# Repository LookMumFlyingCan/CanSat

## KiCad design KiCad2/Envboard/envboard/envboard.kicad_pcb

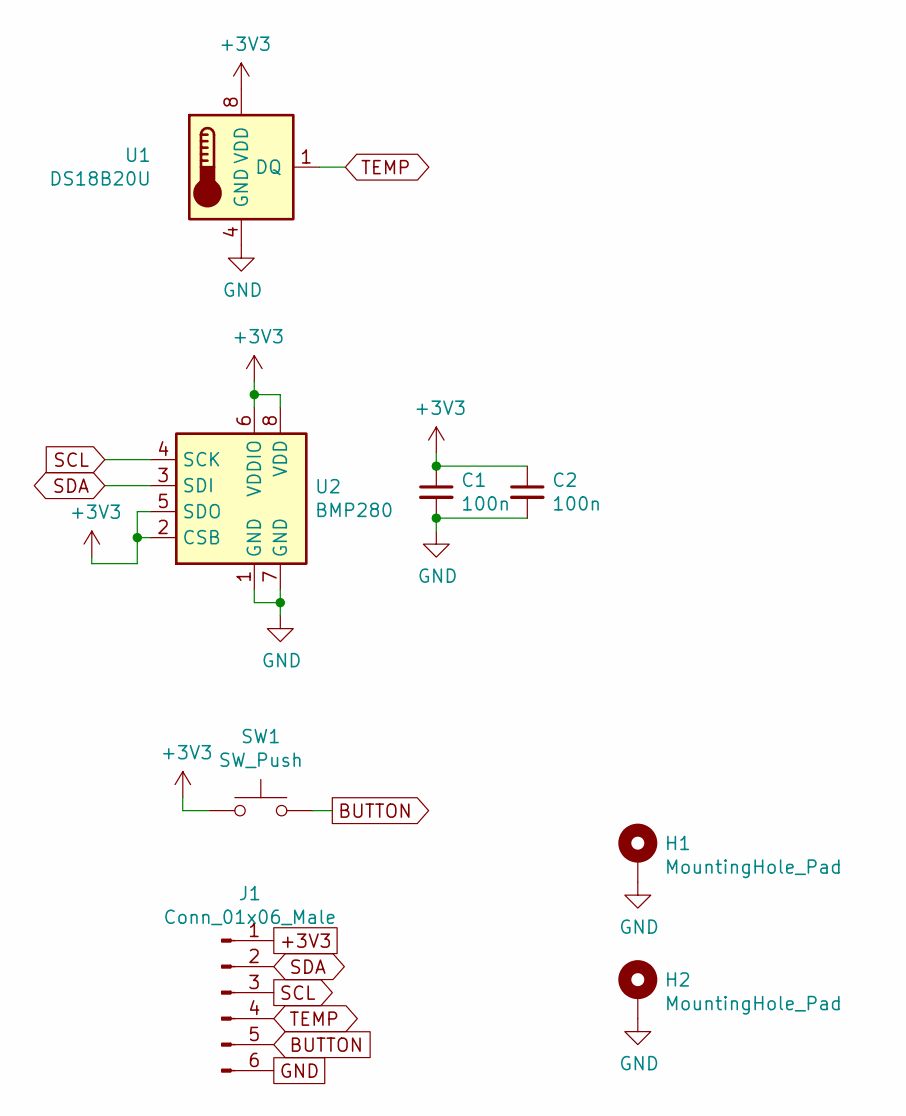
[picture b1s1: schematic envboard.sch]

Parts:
C1, C2: 100n; C_0603_1608Metric
H1, H2: MountingHole_Pad; MountingHole_2.2mm_M2_Pad_Via
J1: Conn_01x06_Male; JST_SH_BM06B-SRSS-TB_1x06-1MP_P1.00mm_Vertical
SW1: SW_Push; SW_SPST_TAEF-25R-V-T
U1: DS18B20U; MSOP-8_3x3mm_P0.65mm
U2: BMP280; Bosch_LGA-8_2x2.5mm_P0.65mm_ClockwisePinNumbering

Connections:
+3V3: C1.1, C2.1, J1.1, SW1.1, U1.8 (VDD), U2.2 (CSB), U2.5 (SDO), U2.6 (VDDIO), U2.8 (VDD)
BUTTON: J1.5, SW1.2
GND: C1.2, C2.2, H1.1, H2.1, J1.6, U1.4 (GND), U2.1 (GND), U2.7 (GND)
SCL: J1.3, U2.4 (SCK)
SDA: J1.2, U2.3 (SDI)
TEMP: J1.4, U1.1 (DQ)

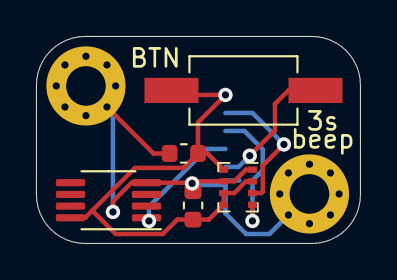
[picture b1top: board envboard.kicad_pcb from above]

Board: 2 copper layers, 18.0 x 11.5 mm, 8 parts (1 on the bottom side), 6 nets.

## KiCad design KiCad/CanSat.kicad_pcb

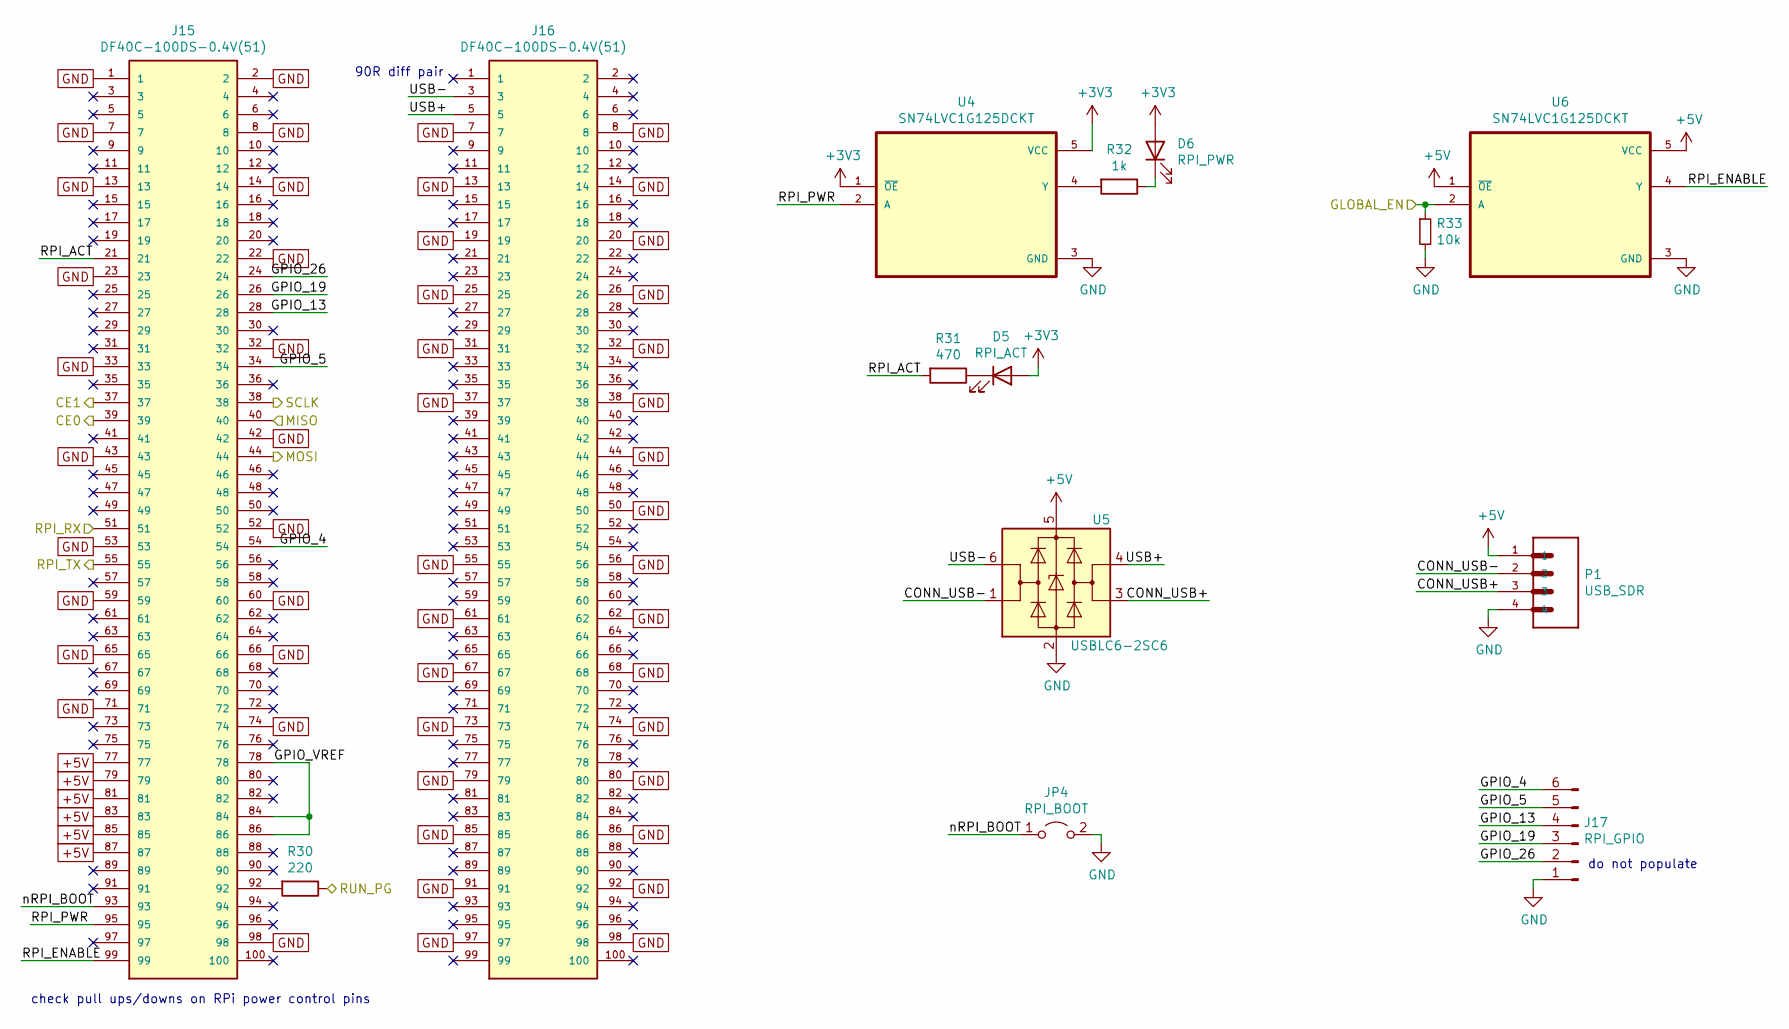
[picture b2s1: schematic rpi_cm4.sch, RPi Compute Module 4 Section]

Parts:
D5: RPI_ACT; LED_0603_1608Metric_Pad1.05x0.95mm_HandSolder
D6: RPI_PWR; LED_0603_1608Metric_Pad1.05x0.95mm_HandSolder
J15, J16: DF40C-100DS-0.4V(51); HRS_DF40C-100DS-0.4V(51)
J17: RPI_GPIO; PinHeader_1x06_P1.00mm_Vertical
JP4: RPI_BOOT; TestPoint_2Pads_Pitch2.54mm_Drill0.8mm
P1: USB_SDR; TE_1734366-1
R30: 220; R_0603_1608Metric_Pad1.05x0.95mm_HandSolder
R31: 470; R_0603_1608Metric_Pad1.05x0.95mm_HandSolder
R32: 1k; R_0603_1608Metric_Pad1.05x0.95mm_HandSolder
R33: 10k; R_0603_1608Metric_Pad1.05x0.95mm_HandSolder
U4, U6: SN74LVC1G125DCKT; SOT65P210X110-5N
U5: USBLC6-2SC6; SOT-23-6

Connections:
+5V: J15.77, J15.79, J15.81, J15.83, J15.85, J15.87, P1.1, U5.5 (VBUS), U6.1 (~OE), U6.5 (VCC); also elsewhere on the board
/Peripherals and Connectors/CLK: J15.38; also elsewhere on the board
/Peripherals and Connectors/MISO: J15.40; also elsewhere on the board
/Peripherals and Connectors/MOSI: J15.44; also elsewhere on the board
/RPi CM4/CE0: J15.39; also elsewhere on the board
/RPi CM4/CE1: J15.37; also elsewhere on the board
/RPi CM4/CONN_USB+: P1.3, U5.3 (I/O2)
/RPi CM4/CONN_USB-: P1.2, U5.1 (I/O1)
/RPi CM4/GLOBAL_EN: R33.1, U6.2 (A); also elsewhere on the board
/RPi CM4/GPIO_4: J15.54, J17.6
/RPi CM4/GPIO_5: J15.34, J17.5
/RPi CM4/GPIO_13: J15.28, J17.4
/RPi CM4/GPIO_19: J15.26, J17.3
/RPi CM4/GPIO_26: J15.24, J17.2
/RPi CM4/GPIO_VREF: J15.78, J15.84, J15.86
/RPi CM4/RPI_ACT: J15.21, R31.2
/RPi CM4/RPI_ENABLE: J15.99, U6.4 (Y)
/RPi CM4/RPI_PWR: J15.95, U4.2 (A)
/RPi CM4/RPI_RX: J15.51; also elsewhere on the board
/RPi CM4/RPI_TX: J15.55; also elsewhere on the board
/RPi CM4/RUN_PG: R30.1; also elsewhere on the board
/RPi CM4/USB+: J16.5, U5.4 (I/O2)
/RPi CM4/USB-: J16.3, U5.6 (I/O1)
/RPi CM4/nRPI_BOOT: J15.93, JP4.1 (A)
unnamed: D5.1 (K), R31.1
unnamed: D6.1 (K), R32.1
unnamed: J15.92, R30.2
unnamed: R32.2, U4.4 (Y)

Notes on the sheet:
90R diff pair
check pull ups/downs on RPi power control pins
do not populate

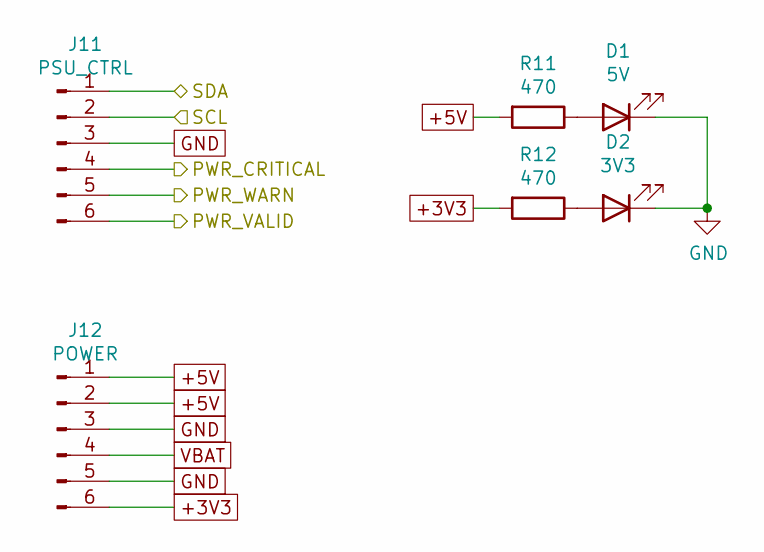
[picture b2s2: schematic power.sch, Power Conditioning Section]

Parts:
D1: 5V; LED_0603_1608Metric_Pad1.05x0.95mm_HandSolder
D2: 3V3; LED_0603_1608Metric_Pad1.05x0.95mm_HandSolder
J11: PSU_CTRL; JST_SH_BM06B-SRSS-TB_1x06-1MP_P1.00mm_Vertical
J12: POWER; JST_PH_S6B-PH-K_1x06_P2.00mm_Horizontal
R11, R12: 470; R_0603_1608Metric_Pad1.05x0.95mm_HandSolder

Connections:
+5V: J12.1, J12.2, R11.2; also elsewhere on the board
/Peripherals and Connectors/SCL: J11.5; also elsewhere on the board
/Peripherals and Connectors/SDA: J11.6; also elsewhere on the board
/Power/PWR_VALID: J11.1; also elsewhere on the board
/Power/PWR_WARN: J11.2; also elsewhere on the board
unnamed: D1.2 (A), R11.1
unnamed: D2.2 (A), R12.1
VBAT: J12.4; also elsewhere on the board

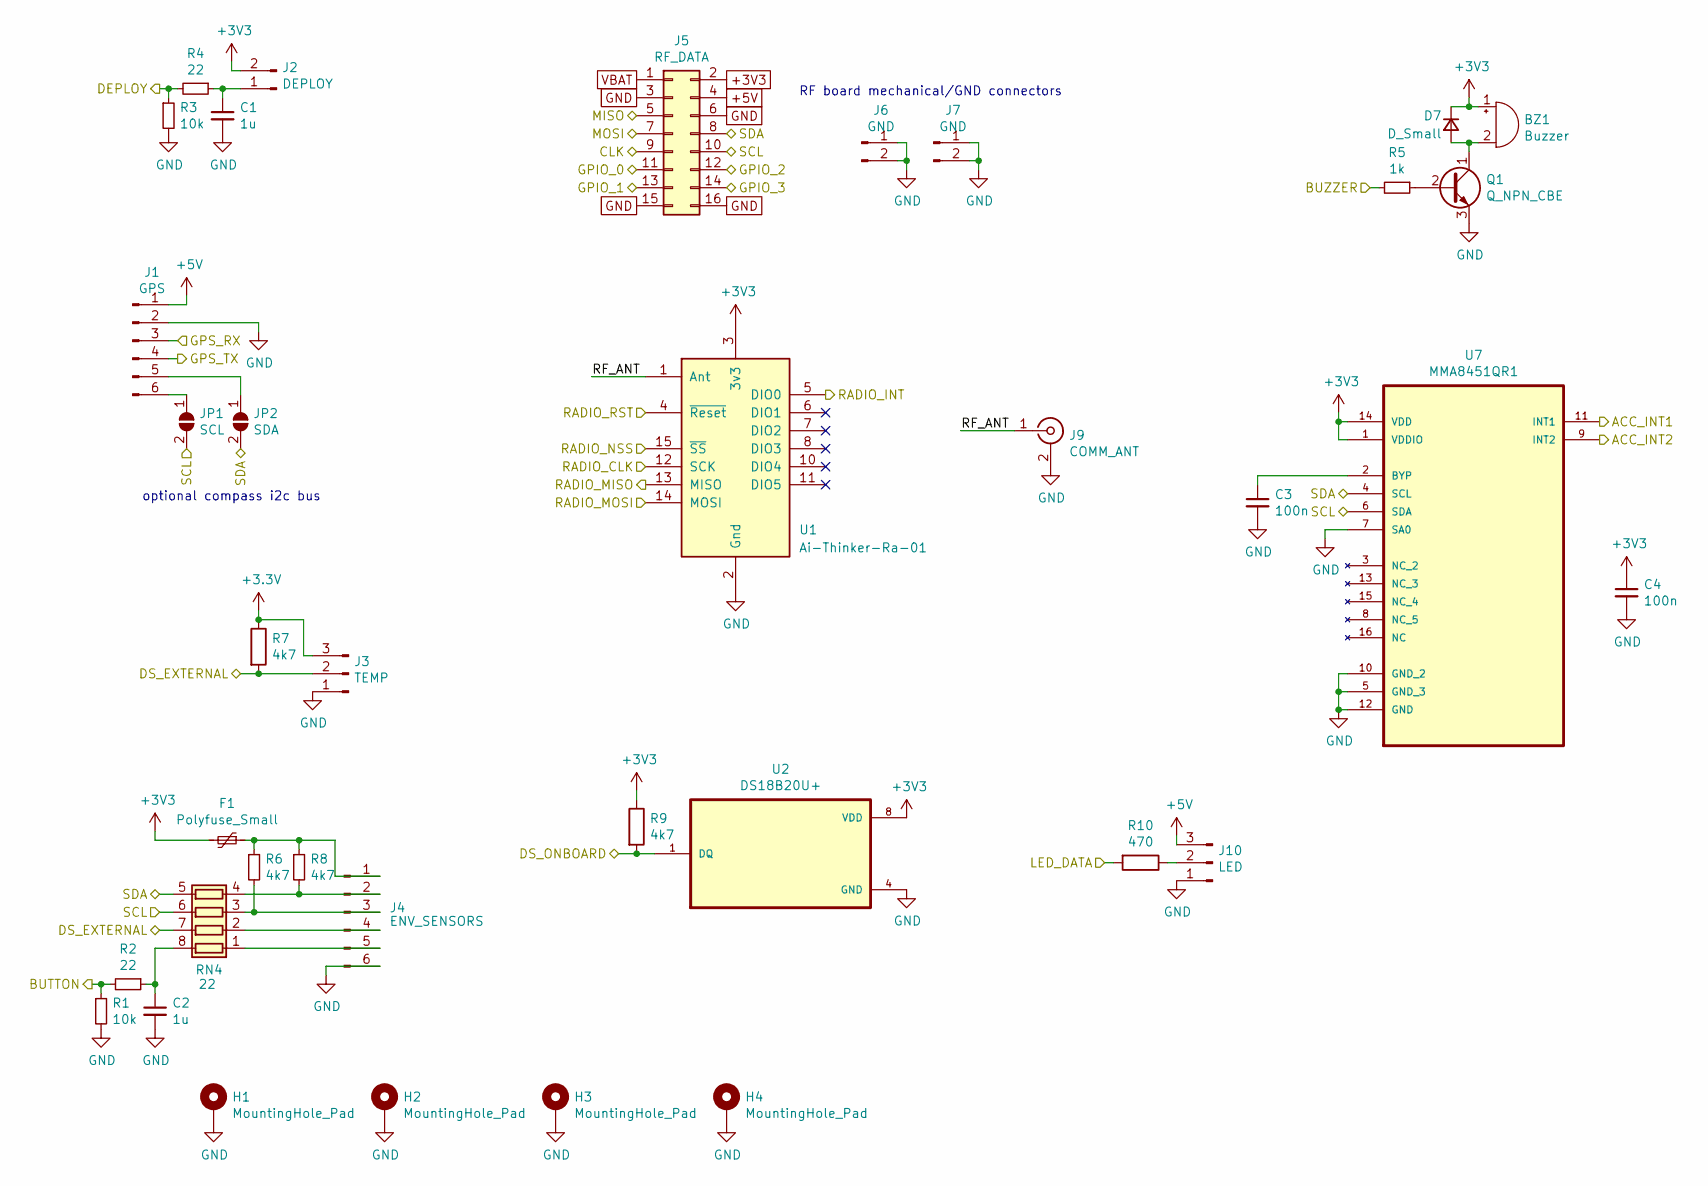
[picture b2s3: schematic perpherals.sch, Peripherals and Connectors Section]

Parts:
BZ1: Buzzer; MagneticBuzzer_INGHAi_GSC4417YA-16R4000
C1, C2: 1u; C_0603_1608Metric_Pad1.05x0.95mm_HandSolder
C3, C4: 100n; C_0603_1608Metric_Pad1.05x0.95mm_HandSolder
D7: D_Small; D_0603_1608Metric_Pad1.05x0.95mm_HandSolder
F1: Polyfuse_Small; Fuse_0603_1608Metric_Pad1.05x0.95mm_HandSolder
H1, H2, H3, H4: MountingHole_Pad; MountingHole_2.7mm_M2.5_Pad_Via
J1: GPS; JST_SH_SM06B-SRSS-TB_1x06-1MP_P1.00mm_Horizontal
J2: DEPLOY; JST_SH_SM02B-SRSS-TB_1x02-1MP_P1.00mm_Horizontal
J3: TEMP; JST_SH_SM03B-SRSS-TB_1x03-1MP_P1.00mm_Horizontal
J4: ENV_SENSORS; JST_SH_SM06B-SRSS-TB_1x06-1MP_P1.00mm_Horizontal
J5: RF_DATA; PinHeader_2x08_P1.27mm_Vertical_SMD
J6, J7: GND; PinHeader_1x02_P2.54mm_Vertical
J9: COMM_ANT; U.FL_Molex_MCRF_73412-0110_Vertical
J10: LED; PinHeader_1x03_P2.54mm_Horizontal
JP1: SCL; SolderJumper-2_P1.3mm_Open_TrianglePad1.0x1.5mm
JP2: SDA; SolderJumper-2_P1.3mm_Open_TrianglePad1.0x1.5mm
Q1: Q_NPN_CBE; SOT-23
R1, R3: 10k; R_0603_1608Metric_Pad1.05x0.95mm_HandSolder
R2, R4: 22; R_0603_1608Metric_Pad1.05x0.95mm_HandSolder
R5: 1k; R_0603_1608Metric_Pad1.05x0.95mm_HandSolder
R6, R7, R8, R9: 4k7; R_0603_1608Metric_Pad1.05x0.95mm_HandSolder
R10: 470; R_0603_1608Metric_Pad1.05x0.95mm_HandSolder
RN4: 22; R_Array_Concave_4x0603
U1: Ai-Thinker-Ra-01; Ai-Thinker-Ra-01-LoRa
U2: DS18B20U+; SOP65P490X110-8N
U7: MMA8451QR1; QFN50P300X300X100-16N; MPN MMA8451QR1

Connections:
+5V: J1.1, J5.4, J10.3; also elsewhere on the board
/Peripherals and Connectors/ACC_INT1: U7.11 (INT1); also elsewhere on the board
/Peripherals and Connectors/ACC_INT2: U7.9 (INT2); also elsewhere on the board
/Peripherals and Connectors/BUTTON: R1.1, R2.2; also elsewhere on the board
/Peripherals and Connectors/BUZZER: R5.2; also elsewhere on the board
/Peripherals and Connectors/CLK: J5.9; also elsewhere on the board
/Peripherals and Connectors/DEPLOY: R3.1, R4.2; also elsewhere on the board
/Peripherals and Connectors/DS_EXTERNAL: J3.2, R7.2, R9.2, RN4.7 (R2.2), U2.1 (DQ); also elsewhere on the board
/Peripherals and Connectors/GPIO_2: J5.12; also elsewhere on the board
/Peripherals and Connectors/GPIO_3: J5.14; also elsewhere on the board
/Peripherals and Connectors/GPS_RX: J1.3; also elsewhere on the board
/Peripherals and Connectors/GPS_TX: J1.4; also elsewhere on the board
/Peripherals and Connectors/LED_DATA: R10.2; also elsewhere on the board
/Peripherals and Connectors/MISO: J5.5; also elsewhere on the board
/Peripherals and Connectors/MOSI: J5.7; also elsewhere on the board
/Peripherals and Connectors/RADIO_CLK: U1.12 (SCK); also elsewhere on the board
/Peripherals and Connectors/RADIO_INT: U1.5 (DIO0); also elsewhere on the board
/Peripherals and Connectors/RADIO_MISO: U1.13 (MISO); also elsewhere on the board
/Peripherals and Connectors/RADIO_MOSI: U1.14 (MOSI); also elsewhere on the board
/Peripherals and Connectors/RADIO_NSS: U1.15 (~SS); also elsewhere on the board
/Peripherals and Connectors/RADIO_RST: U1.4 (~Reset); also elsewhere on the board
/Peripherals and Connectors/RF_ANT: J9.1 (In), U1.1 (Ant)
/Peripherals and Connectors/SCL: J5.10, JP1.2 (B), RN4.6 (R3.2), U7.6 (SDA); also elsewhere on the board
/Peripherals and Connectors/SDA: J5.8, JP2.2 (B), RN4.5 (R4.2), U7.4 (SCL); also elsewhere on the board
/RPi CM4/CE0: J5.11; also elsewhere on the board
/RPi CM4/CE1: J5.13; also elsewhere on the board
unnamed: BZ1.2 (+), D7.2 (A), Q1.1 (C)
unnamed: C1.1, J2.1, R4.1
unnamed: C2.1, R2.1, RN4.8 (R1.2)
unnamed: C3.1, U7.2 (BYP)
unnamed: F1.1, J4.1, R6.1, R8.1
unnamed: J1.5, JP2.1 (A)
unnamed: J1.6, JP1.1 (A)
unnamed: J4.2, R8.2, RN4.4 (R4.1)
unnamed: J4.3, R6.2, RN4.3 (R3.1)
unnamed: J4.4, RN4.2 (R2.1)
unnamed: J4.5, RN4.1 (R1.1)
unnamed: J10.2, R10.1
unnamed: Q1.2 (B), R5.1
VBAT: J5.1; also elsewhere on the board

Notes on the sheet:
optional compass i2c bus
RF board mechanical/GND connectors

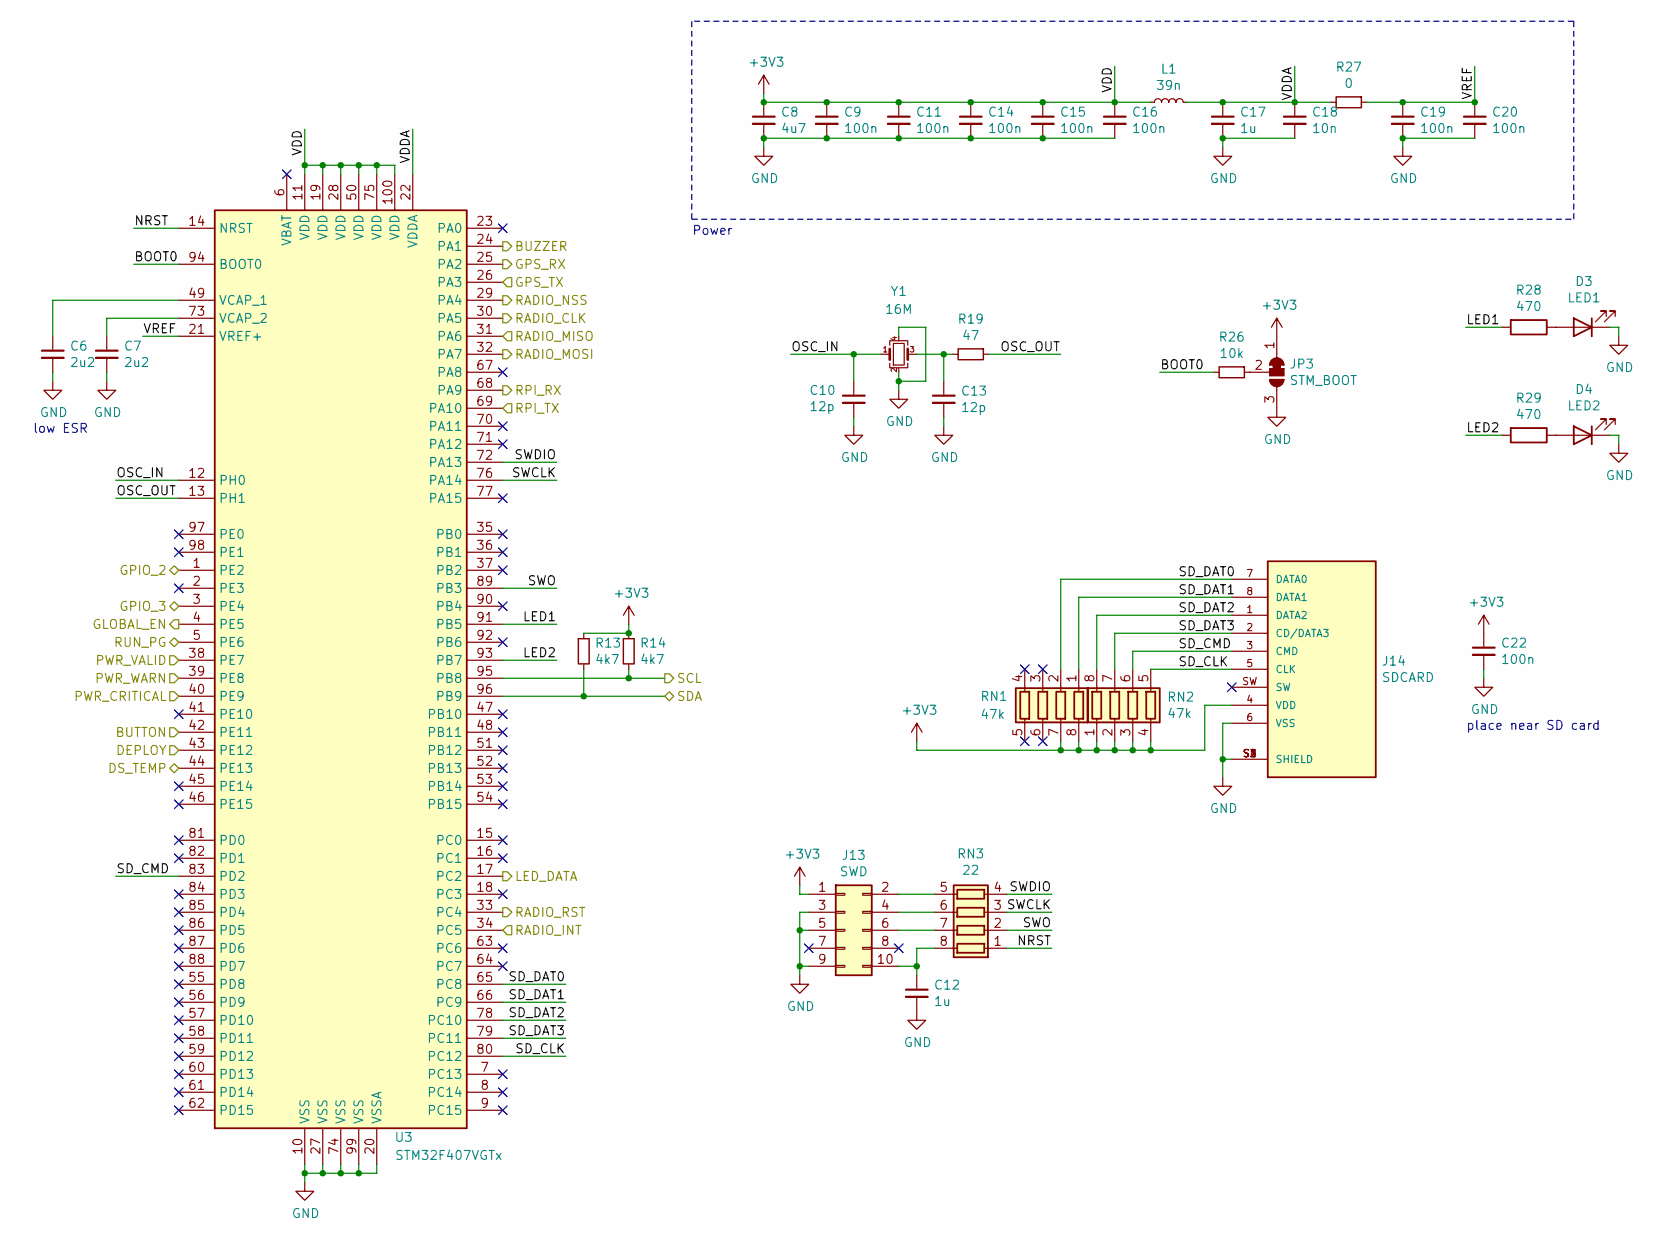
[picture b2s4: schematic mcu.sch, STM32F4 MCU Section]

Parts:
C6, C7: 2u2; C_0603_1608Metric_Pad1.05x0.95mm_HandSolder
C8: 4u7; C_0603_1608Metric_Pad1.05x0.95mm_HandSolder
C9, C11, C14, C15, C16, C19, C20, C22: 100n; C_0603_1608Metric_Pad1.05x0.95mm_HandSolder
C10, C13: 12p; C_0603_1608Metric_Pad1.05x0.95mm_HandSolder
C12, C17: 1u; C_0603_1608Metric_Pad1.05x0.95mm_HandSolder
C18: 10n; C_0603_1608Metric_Pad1.05x0.95mm_HandSolder
D3: LED1; LED_0603_1608Metric_Pad1.05x0.95mm_HandSolder
D4: LED2; LED_0603_1608Metric_Pad1.05x0.95mm_HandSolder
J13: SWD; PinHeader_2x05_P1.27mm_Vertical_SMD
J14: SDCARD; MOLEX_47352-1001; PARTREV K
JP3: STM_BOOT; SolderJumper-3_P1.3mm_Bridged12_RoundedPad1.0x1.5mm
L1: 39n; L_0603_1608Metric_Pad1.05x0.95mm_HandSolder
R13, R14: 4k7; R_0603_1608Metric_Pad1.05x0.95mm_HandSolder
R19: 47; R_0603_1608Metric_Pad1.05x0.95mm_HandSolder
R26: 10k; R_0603_1608Metric_Pad1.05x0.95mm_HandSolder
R27: 0; R_0805_2012Metric_Pad1.15x1.40mm_HandSolder
R28, R29: 470; R_0603_1608Metric_Pad1.05x0.95mm_HandSolder
RN1, RN2: 47k; R_Array_Concave_4x0603
RN3: 22; R_Array_Concave_4x0603
U3: STM32F407VGTx; LQFP-100_14x14mm_P0.5mm
Y1: 16M; Crystal_SMD_3225-4Pin_3.2x2.5mm_HandSoldering

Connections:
/Peripherals and Connectors/ACC_INT1: U3.52 (PB13); also elsewhere on the board
/Peripherals and Connectors/ACC_INT2: U3.51 (PB12); also elsewhere on the board
/Peripherals and Connectors/BUTTON: U3.42 (PE11); also elsewhere on the board
/Peripherals and Connectors/BUZZER: U3.24 (PA1); also elsewhere on the board
/Peripherals and Connectors/DEPLOY: U3.43 (PE12); also elsewhere on the board
/Peripherals and Connectors/DS_EXTERNAL: U3.44 (PE13); also elsewhere on the board
/Peripherals and Connectors/GPIO_2: U3.1 (PE2); also elsewhere on the board
/Peripherals and Connectors/GPIO_3: U3.3 (PE4); also elsewhere on the board
/Peripherals and Connectors/GPS_RX: U3.25 (PA2); also elsewhere on the board
/Peripherals and Connectors/GPS_TX: U3.26 (PA3); also elsewhere on the board
/Peripherals and Connectors/LED_DATA: U3.17 (PC2); also elsewhere on the board
/Peripherals and Connectors/RADIO_CLK: U3.30 (PA5); also elsewhere on the board
/Peripherals and Connectors/RADIO_INT: U3.34 (PC5); also elsewhere on the board
/Peripherals and Connectors/RADIO_MISO: U3.31 (PA6); also elsewhere on the board
/Peripherals and Connectors/RADIO_MOSI: U3.32 (PA7); also elsewhere on the board
/Peripherals and Connectors/RADIO_NSS: U3.29 (PA4); also elsewhere on the board
/Peripherals and Connectors/RADIO_RST: U3.33 (PC4); also elsewhere on the board
/Peripherals and Connectors/SCL: R14.2, U3.95 (PB8); also elsewhere on the board
/Peripherals and Connectors/SDA: R13.2, U3.96 (PB9); also elsewhere on the board
/Power/PWR_VALID: U3.38 (PE7); also elsewhere on the board
/Power/PWR_WARN: U3.39 (PE8); also elsewhere on the board
/RPi CM4/GLOBAL_EN: U3.4 (PE5); also elsewhere on the board
/RPi CM4/RPI_RX: U3.68 (PA9); also elsewhere on the board
/RPi CM4/RPI_TX: U3.69 (PA10); also elsewhere on the board
/RPi CM4/RUN_PG: U3.5 (PE6); also elsewhere on the board
/STM32 MCU/BOOT0: R26.2, U3.94 (BOOT0)
/STM32 MCU/LED1: R28.2, U3.91 (PB5)
/STM32 MCU/LED2: R29.2, U3.93 (PB7)
/STM32 MCU/NRST: RN3.1 (R1.1), U3.14 (NRST)
/STM32 MCU/OSC_IN: C10.1, U3.12 (PH0), Y1.1
/STM32 MCU/OSC_OUT: R19.1, U3.13 (PH1)
/STM32 MCU/SD_CLK: J14.5 (CLK), RN2.5 (R4.2), U3.80 (PC12)
/STM32 MCU/SD_CMD: J14.3 (CMD), RN2.6 (R3.2), U3.83 (PD2)
/STM32 MCU/SD_DAT0: J14.7 (DATA0), RN1.2 (R2.1), U3.65 (PC8)
/STM32 MCU/SD_DAT1: J14.8 (DATA1), RN1.1 (R1.1), U3.66 (PC9)
/STM32 MCU/SD_DAT2: J14.1 (DATA2), RN2.8 (R1.2), U3.78 (PC10)
/STM32 MCU/SD_DAT3: J14.2 (CD/DATA3), RN2.7 (R2.2), U3.79 (PC11)
/STM32 MCU/SWCLK: RN3.3 (R3.1), U3.76 (PA14)
/STM32 MCU/SWDIO: RN3.4 (R4.1), U3.72 (PA13)
/STM32 MCU/SWO: RN3.2 (R2.1), U3.89 (PB3)
/STM32 MCU/VDDA: C17.1, C18.1, L1.2, R27.2, U3.22 (VDDA)
/STM32 MCU/VREF: C19.1, C20.1, R27.1, U3.21 (VREF+)
unnamed: C6.1, U3.49 (VCAP_1)
unnamed: C7.1, U3.73 (VCAP_2)
unnamed: C12.1, J13.10, RN3.8 (R1.2)
unnamed: C13.1, R19.2, Y1.3
unnamed: D3.2 (A), R28.1
unnamed: D4.2 (A), R29.1
unnamed: J13.2, RN3.5 (R4.2)
unnamed: J13.4, RN3.6 (R3.2)
unnamed: J13.6, RN3.7 (R2.2)
unnamed: JP3.2 (C), R26.1

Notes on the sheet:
low ESR
Power
place near SD card

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
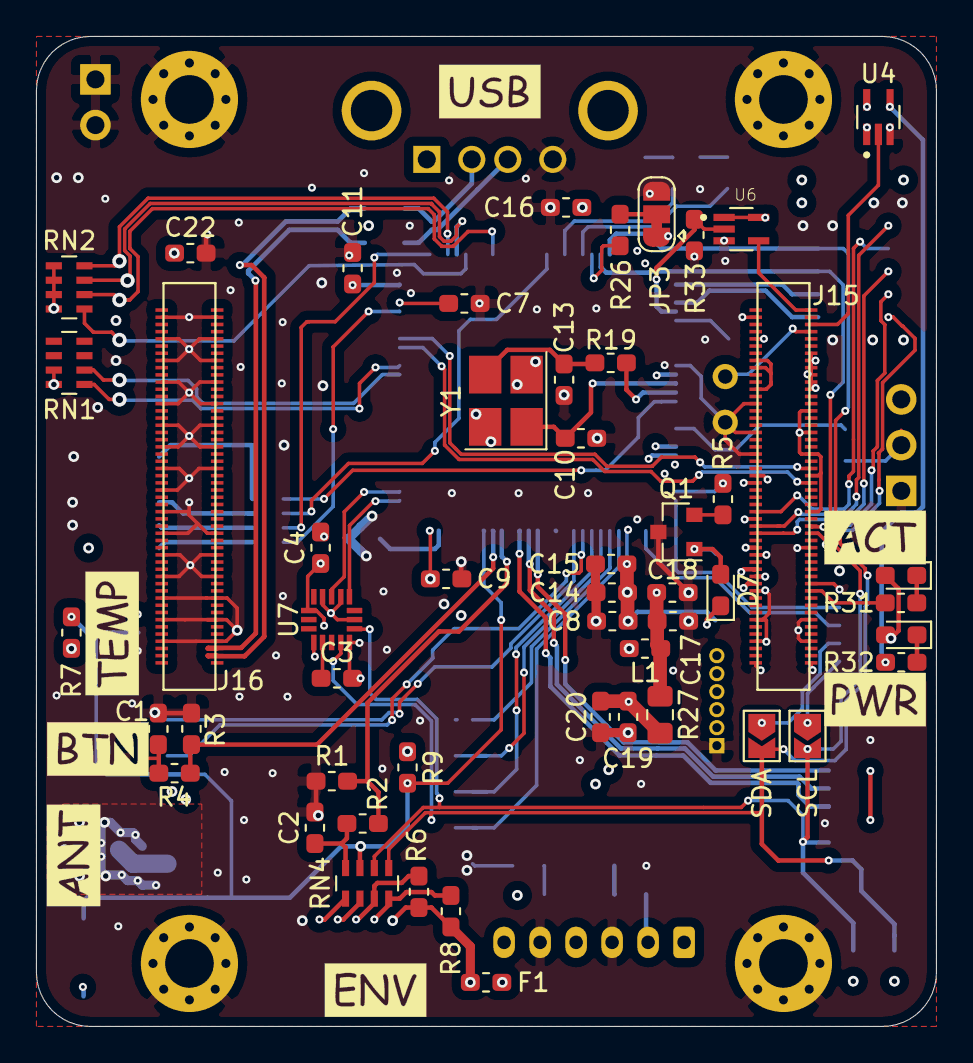
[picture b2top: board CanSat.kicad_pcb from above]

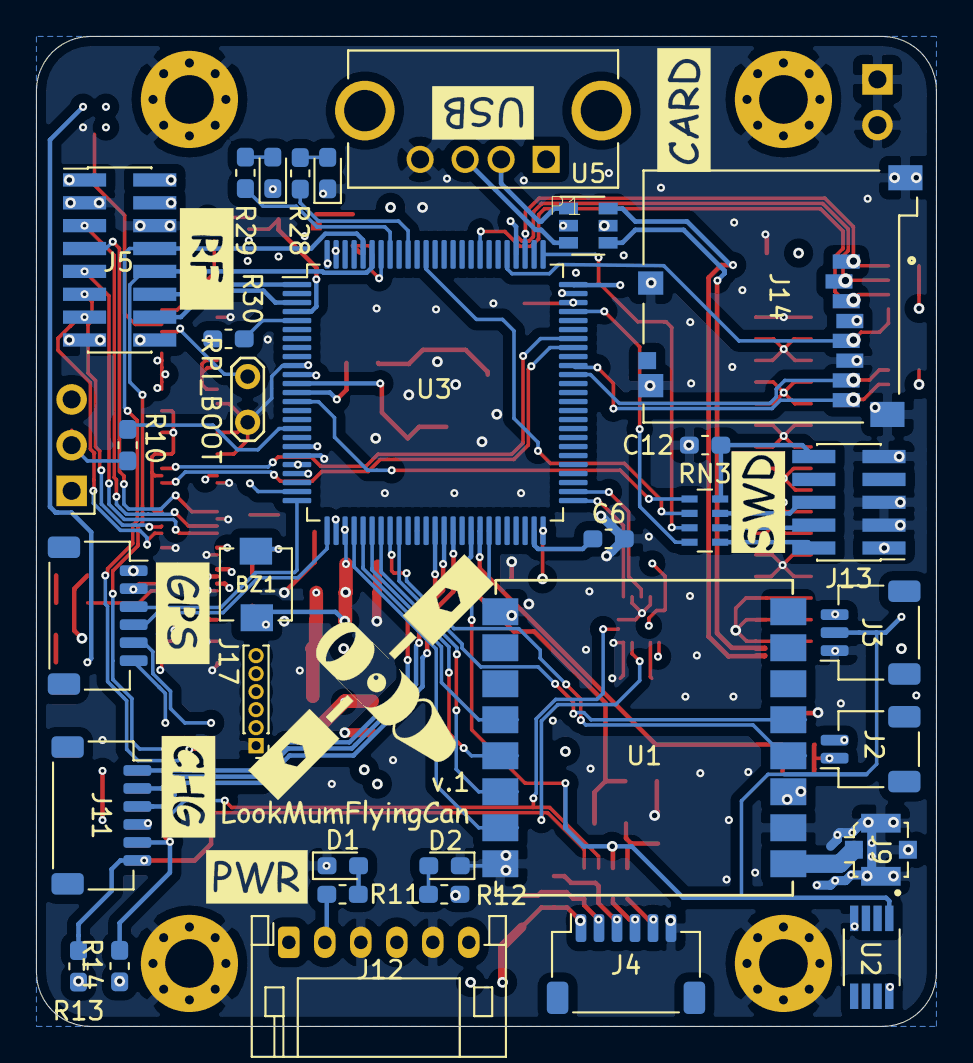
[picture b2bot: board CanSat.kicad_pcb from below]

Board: 4 copper layers, 50.0 x 55.0 mm, 90 parts (34 on the bottom side), 96 nets.

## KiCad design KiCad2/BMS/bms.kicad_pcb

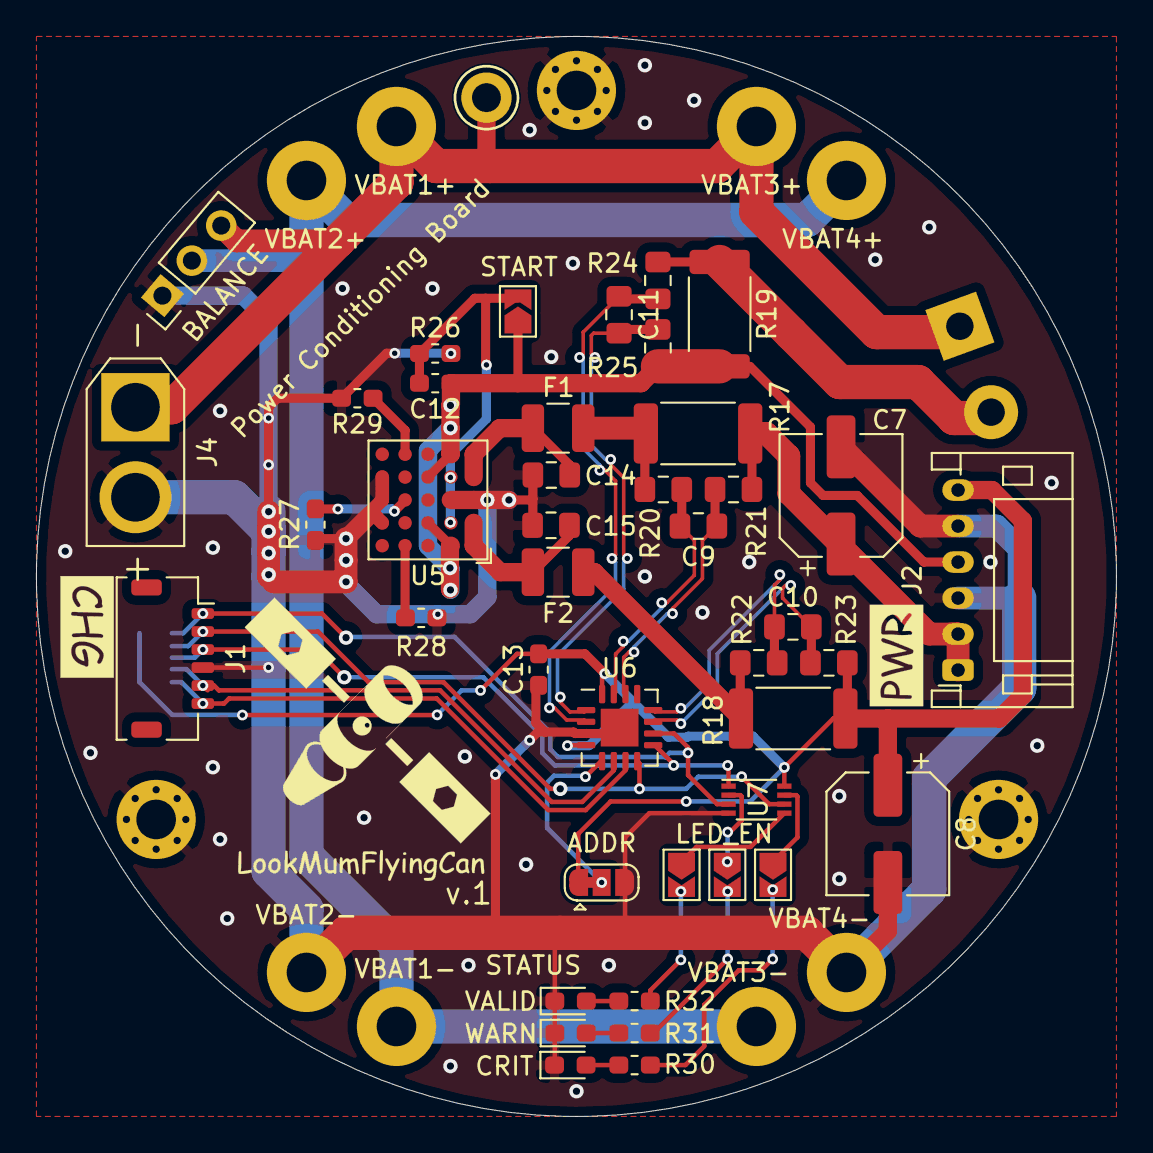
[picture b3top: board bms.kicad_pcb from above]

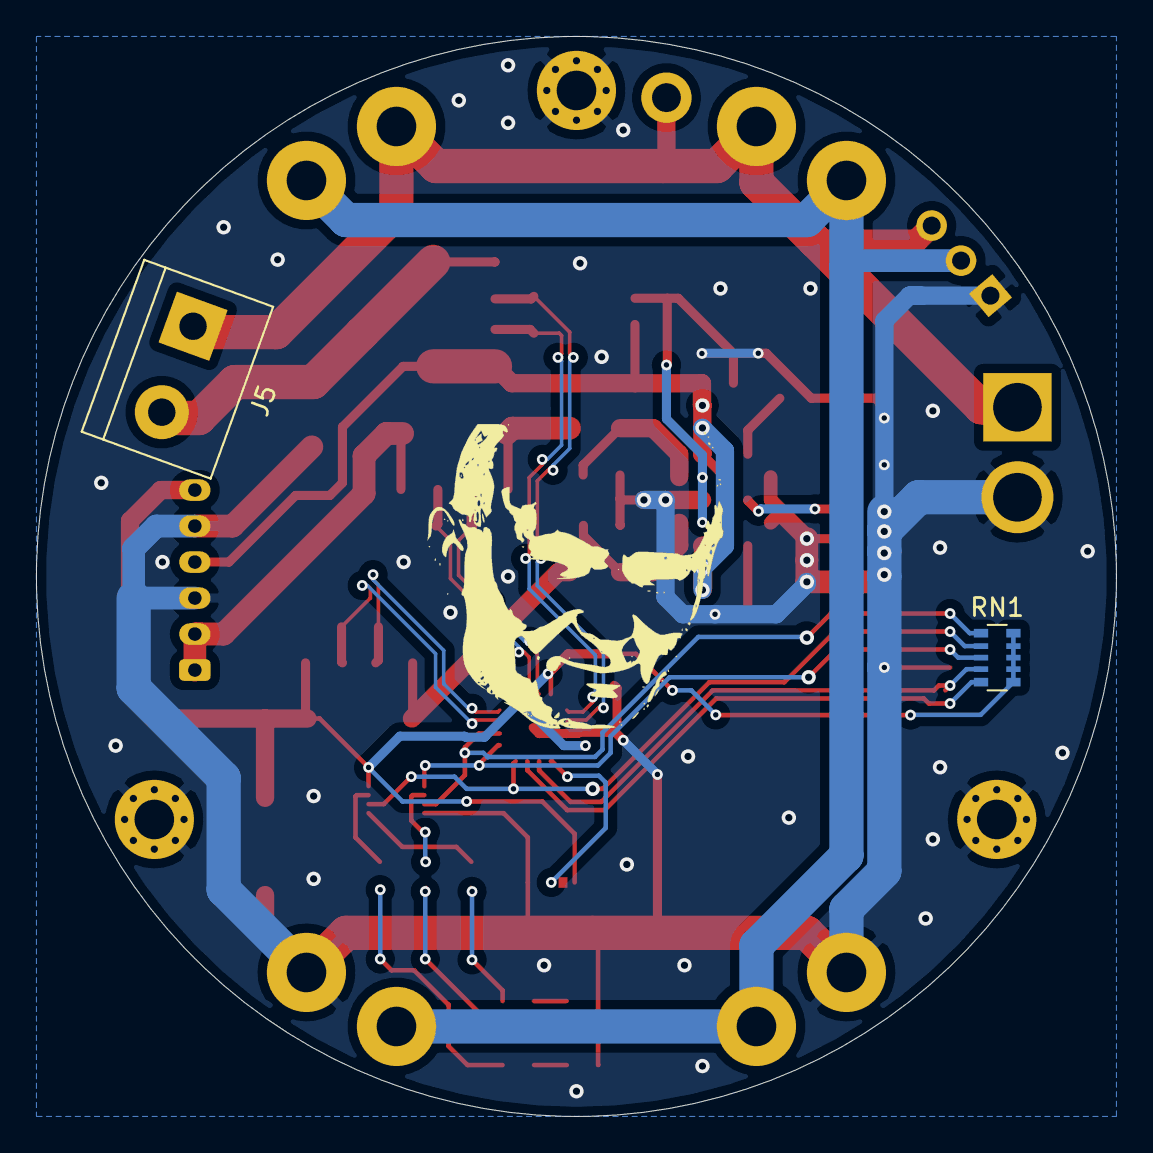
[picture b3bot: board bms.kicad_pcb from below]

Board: 2 copper layers, 60.0 x 60.0 mm, 56 parts (2 on the bottom side), 36 nets.

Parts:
ADDR: A0; SolderJumper-3_P1.3mm_Bridged12_RoundedPad1.0x1.5mm
BALANCE: BALANCE; PinHeader_1x03_P2.54mm_Vertical
C7, C8: 150u; CP_Elec_6.3x5.8
C9, C10, C11: 500p; C_0805_2012Metric_Pad1.15x1.40mm_HandSolder
C12: 10u; C_0603_1608Metric_Pad1.05x0.95mm_HandSolder
C13: 100n; C_0603_1608Metric_Pad1.05x0.95mm_HandSolder
C14, C15: 10u; C_0805_2012Metric_Pad1.15x1.40mm_HandSolder
CRIT: DIGITAL_CRITICAL; LED_0603_1608Metric_Pad1.05x0.95mm_HandSolder
F1, F2: 1210L150/16WR; Fuse_1210_3225Metric
H9, H11: MountingHole; MountingHole_2.2mm_M2_Pad_Via
He: MountingHole; MountingHole_2.2mm_M2_Pad_Via
J1: PSU_CTRL; JST_SHL_SM06B-SHLS-TF_1x06-1MP_P1.00mm_Horizontal
J2: PWR; JST_PH_S6B-PH-K_1x06_P2.00mm_Horizontal
J4: CHARGE; AMASS_XT30U-F_1x02_P5.0mm_Vertical
J5: PWR; TerminalBlock_bornier-2_P5.08mm
JP3, JP4, JP5: SolderJumper_2_Open; SolderJumper-2_P1.3mm_Open_TrianglePad1.0x1.5mm
R17: 0.05; R_2512_6332Metric
R18, R19: 0.08; R_2512_6332Metric
R20, R21, R22, R23, R24, R25: 5; R_0805_2012Metric_Pad1.15x1.40mm_HandSolder
R26: 47k; R_0603_1608Metric_Pad1.05x0.95mm_HandSolder
R27: 215k; R_0603_1608Metric_Pad1.05x0.95mm_HandSolder
R28: 13k3; R_0603_1608Metric_Pad1.05x0.95mm_HandSolder
R29: 8k25; R_0603_1608Metric_Pad1.05x0.95mm_HandSolder
R30, R31: 1k; R_0603_1608Metric_Pad1.05x0.95mm_HandSolder
R32: 470; R_0603_1608Metric_Pad1.05x0.95mm_HandSolder
RN1: R_Pack05; R_Array_Convex_5x0603
START: 0; SolderJumper-2_P1.3mm_Open_TrianglePad1.0x1.5mm
TP1: +BATT; TestPoint_Keystone_5010-5014_Multipurpose
U5: LTM4622EYPBF; BGA-25_6.35x6.35mm_Layout5x5_P1.27mm
U6: INA3221; Texas_RGV_S-PVQFN-N16_EP2.1x2.1mm
U7: 74LVC3G04; VSSOP-8_2.3x2mm_P0.5mm
VALID: DIGITAL_PV; LED_0603_1608Metric_Pad1.05x0.95mm_HandSolder
VBAT1+: VBAT1+; MountingHole_2.2mm_M2_Pad
VBAT1-: VBAT1-; MountingHole_2.2mm_M2_Pad
VBAT2+: VBAT2+; MountingHole_2.2mm_M2_Pad
VBAT2-: VBAT2-; MountingHole_2.2mm_M2_Pad
VBAT3+: VBAT3+; MountingHole_2.2mm_M2_Pad
VBAT3-: VBAT3-; MountingHole_2.2mm_M2_Pad
VBAT4+: VBAT4+; MountingHole_2.2mm_M2_Pad
VBAT4-: VBAT4-; MountingHole_2.2mm_M2_Pad
WARN: DIGITAL_WARNING; LED_0603_1608Metric_Pad1.05x0.95mm_HandSolder

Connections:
+3V3: ADDR.1, C8.1, C13.1, J2.6, R18.2, R23.2, RN1.6, RN1.7, RN1.8, RN1.9, RN1.10, U6.4, U6.16, U7.8
+5V: C7.1, J2.1, J2.2, R17.2, R21.2
+BATT: BALANCE.3, J4.1, J5.1, TP1.1, VBAT1+.1, VBAT3+.1
A0: ADDR.2, U6.5
BAT: C12.1, J2.4, R19.2, R25.2, START.1, U5.A2, U5.B3, U5.D3, U5.E2
GND: ADDR.3, BALANCE.1, C7.2, C8.2, C13.2, C14.2, C15.2, CRIT.1, H9.1, H11.1, He.1, J1.4, J2.3, J2.5, J4.2, R26.2, R27.1, R28.2, R29.2, U5.B5, U5.C1, U5.C2, U5.C5, U5.D5, U6.3, U6.17, U7.4, VALID.1, VBAT2-.1, VBAT4-.1, WARN.1
IN1+: C10.1, R22.1, U6.12
IN1-: C10.2, R23.1, U6.11
IN2+: C9.1, R20.1, U6.15
IN2-: C9.2, R21.1, U6.14
IN3+: C11.1, R24.1, U6.2
IN3-: C11.2, R25.1, U6.1
LTM_3V3: F2.1, R18.1, R22.2
LTM_5V: F1.1, R17.1, R20.2
unnamed: C12.2, R26.1, START.2, U5.B2, U5.D2
unnamed: C14.1, F1.2, U5.D1, U5.E1
unnamed: C15.1, F2.2, U5.A1, U5.B1
unnamed: CRIT.2, R30.1
unnamed: R31.1, WARN.2
unnamed: R32.1, VALID.2
unnamed: J5.2, R19.1, R24.2
unnamed: JP3.1, U7.7
unnamed: JP3.2, R30.2
unnamed: JP4.1, U7.2
unnamed: JP4.2, R31.2
unnamed: JP5.1, U7.5
unnamed: JP5.2, R32.2
unnamed: R27.2, U5.C4
unnamed: R28.1, U5.A4
unnamed: R29.1, U5.E4
PWR_CRITICAL: J1.3, RN1.3, U6.9, U7.1
PWR_VALID: J1.1, RN1.1, U6.10, U7.3
PWR_WARN: J1.2, RN1.2, U6.8, U7.6
SCL: J1.5, RN1.4, U6.6
SDA: J1.6, RN1.5, U6.7
VBAT1-: BALANCE.2, VBAT1-.1, VBAT2+.1, VBAT3-.1, VBAT4+.1

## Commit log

2020-11-13 Add part libs
2020-12-04 WIP KiCad Flight Computer Schematic
2020-12-04 Update schematic
2020-12-06 Finalized schematic and created S/F associations
2020-12-07 Done some stuff
2020-12-07 FC PCB components layout
2020-12-09 Semi-final flight computer version
2020-12-11 Updated page labels
2020-12-11 Added a button and a buzzer
2020-12-12 Change all SH connectors to horizontal
2020-12-16 Dirty production PCBs commit
2020-12-16 Update .gitignore for KiCad
